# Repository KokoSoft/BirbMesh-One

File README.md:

# BirbMesh-One :bird:

The goal of **Birb**s **Mesh**tastic **One** Watt node project was to create an inexpensive and as small as possible Meshtastic node equipped with a 1 W radio module. An important aspect, from my perspective, is ensuring favorable operating conditions for the battery to extend its lifespan. The project supports multiple configuration variants, and the final functionality depends on the components you choose to solder. The core of the design is the energy‑efficient *nRF52840* controller mounted on a ProMicro board. The project is pin‑compatible with [xiaoWa_pcb](https://github.com/gargomoma/xiaoWa_pcb) and [FakeTec](https://github.com/gargomoma/fakeTec_pcb), which means no custom firmware is required.

**Key features**:
- Compact PCB: 27 × 47 mm
- Support for radio modules: E22(M), Ra‑01SH‑P, HT‑RA62
- Optional LCD and user button support
- Optional battery charging control (hardware or software)
- Optional battery voltage monitoring

## Project Description

The project was inspired by the [ikona nano](https://github.com/ndoo/ikoka-nano-meshtastic-device) and [xiaoWa_pcb](https://github.com/gargomoma/xiaoWa_pcb). The former is based on the Seeed Studio XIAO BLE, which is significantly more expensive than the ProMicro and offers fewer available GPIO pins. Additionally, the board is large and includes connectors for the battery and solar panel, which I found unnecessary. A notable strength is the correct implementation of the power supply for the boost converter that generates the supply voltage for the radio module. Another benefit, in my opinion, is the integration of the converter directly on the PCB, which allows it to be controlled programmatically. This makes it possible to switch it off to save energy. It is a project worth recommending, and using the XIAO BLE may be a good choice for those who prefer not to rely on low‑quality ProMicro boards.

Initially, this project was created as an attempt to solve the power‑supply issue present in xiaoWa_pcb, which requires a connected battery for proper operation. The boost converter powering the radio module draws energy directly from the battery connector. Without a battery, the system is powered solely by the *TP4054* charger IC, which has current limiting and built‑in protections. Although the charging current is configurable, it may be reduced to 1/10 of the set value under certain conditions, making it impossible to use the board with external power only. Using the inexpensive *HW‑085* boost converter module is an interesting idea and certainly simplifies building the device. Unfortunately, it cannot be switched off to save power.

<details>
<summary>Notes from the TP4054 datasheet</summary>

</details>

### Power Supply

There are three possible ways to power the radio module:

#### 1. Power from the ProMicro

To properly power the radio module and minimize energy loss, power must be taken from the switching circuit that selects power between USB voltage (*VBUS*) and battery voltage (*VBAT*). On the schematic, this point is labeled **VDDH**. This ensures that neither the battery nor the charger IC is loaded when device is powered from USB. You must route wire from the indicated point on the ProMicro board to the VDDH pad.

<sub>Image created using a photo from the [nrf52840‑promicro](https://github.com/sasodoma/nrf52840-promicro) repository by [sasodoma](https://github.com/sasodoma).

Optionally, if you want to supply 5 V externally (through connector `J1`) without using USB socket, connect the VBUS pad as well.

#### 2. Independent power‑switching circuit

If you prefer not to draw high current through the questionable‑quality components on the ProMicro, you can build your own voltage‑switching circuit. To do this, solder components `Q1` and `D1`. You must also connect the VBUS pad to allow powering the radio from USB.

#### 3. Compatibility mode with xiaoWa_pcb

If you want to minimize soldering and always use the device with battery connected, you can use this compatibility mode. Short the `JP1` jumper on the bottom of the PCB. The radio will be powered directly from the battery, which will load the charger IC too.

### Boost Converter

High‑power radio modules require a 5 V supply to operate at full output power. This voltage is provided by a boost converter. If you are ordering an assembled board or are comfortable with soldering, the best solution is to build the converter using the *MT3608* IC. Populate components `L1`, `U4`, `D3`, `R11`, `R12`, `C7`, and `C9`.

Alternatively, to avoid soldering small components, you may use the *HW‑085* boost module. In its default configuration, it cannot be disabled to reduce power consumption. However, the project allows adding power control: cut jumper `JP7` (shorted by default) and solder `Q3`, `Q4`, and `R13`.

> [!NOTE]
> If you plan to use a radio module that does not require 5 V (e.g., *HT‑RA62*) or do not need full transmit power, you may omit the boost converter.

### Radio Module

Based on my experience with Meshtastic networks, using an 868 MHz SAW filter significantly improves reception quality, though they have low power tolerance. Cavity filters, on the other hand, are large and expensive. In Europe, the *E22P‑868M30S* module appears to be an ideal solution, offering a built‑in receive‑path filter and high transmit power.

#### E22 / E22P Module

The module supports a wide supply range of 3.3 -- 5 V. Full transmit power requires ≥5 V, so a boost converter is necessary. If full power is not required, you may omit the converter and short *VIN* to *VOUT*. The supply voltage will then equal the battery voltage or approximately 4.7 V when externally powered.

The *T/R CTRL* (*RXEN*) pin is controlled by *SX126x* *DIO2*. The *EN* (*TXEN*) pin is controlled by nRF `P0.17`.

#### Ra‑01SH‑P Module

This module is a cheaper alternative to the E22 series, offering 29/31 dBm output power. However, **it does not include a TCXO**. To achieve full power, 5 V must be supplied to the *VCCPA* pin, requiring a boost converter and shorting pads 1–2 on `JP6`.

> [!IMPORTANT]
> The modules documentation states: _"In the default BOM configuration of the Ra‑01SH‑P module, PA is powered by the 3V3 pin of the module, and the VCCPA pin can be left floating."_

#### HT‑RA62 Module

This module is powered from the ProMicro **EXTVCC** 3.3 V rail. No boost converter is required. Short pads 2–3 on `JP6` to connect *DIO2* to *TXEN*.

### Battery Voltage Monitoring (optional)

The monitoring circuit uses two comparators with hysteresis. U1 (*MIC841H*) asserts reset when battery voltage drops below 3.6 V (\~20% charge). Reset is released above 3.7 V (\~30%).

`U2` limits the maximum charge level. When voltage exceeds 4.05 V (\~80%), the `PROG` pin of the *TP4054* charger is disconnected.

To enable charge control, remove the charging‑current‑setting resistor from the ProMicro.

<sub>Image created using a photo from the [nrf52840‑promicro](https://github.com/sasodoma/nrf52840-promicro) repository by [sasodoma](https://github.com/sasodoma).

Charging current is set by resistor `R8`.

Comparator thresholds are configured using the resistor divider `R2–R5`. Capacitor `C1` filters voltage fluctuations during radio transmission to prevent unwanted resets.

If you do not want hardware‑level reset and charge control but still want battery‑level monitoring in software, install only `R1` and `R2`.

#### Charge Control

To control charging from firmware:

- Remove the charging‑current‑setting resistor from the ProMicro.
- Install `R8` to set the desired charging current.
- Short `JP5` or install `Q2`.

## Ordering the PCBs
## Preparing firmware
## Soldering

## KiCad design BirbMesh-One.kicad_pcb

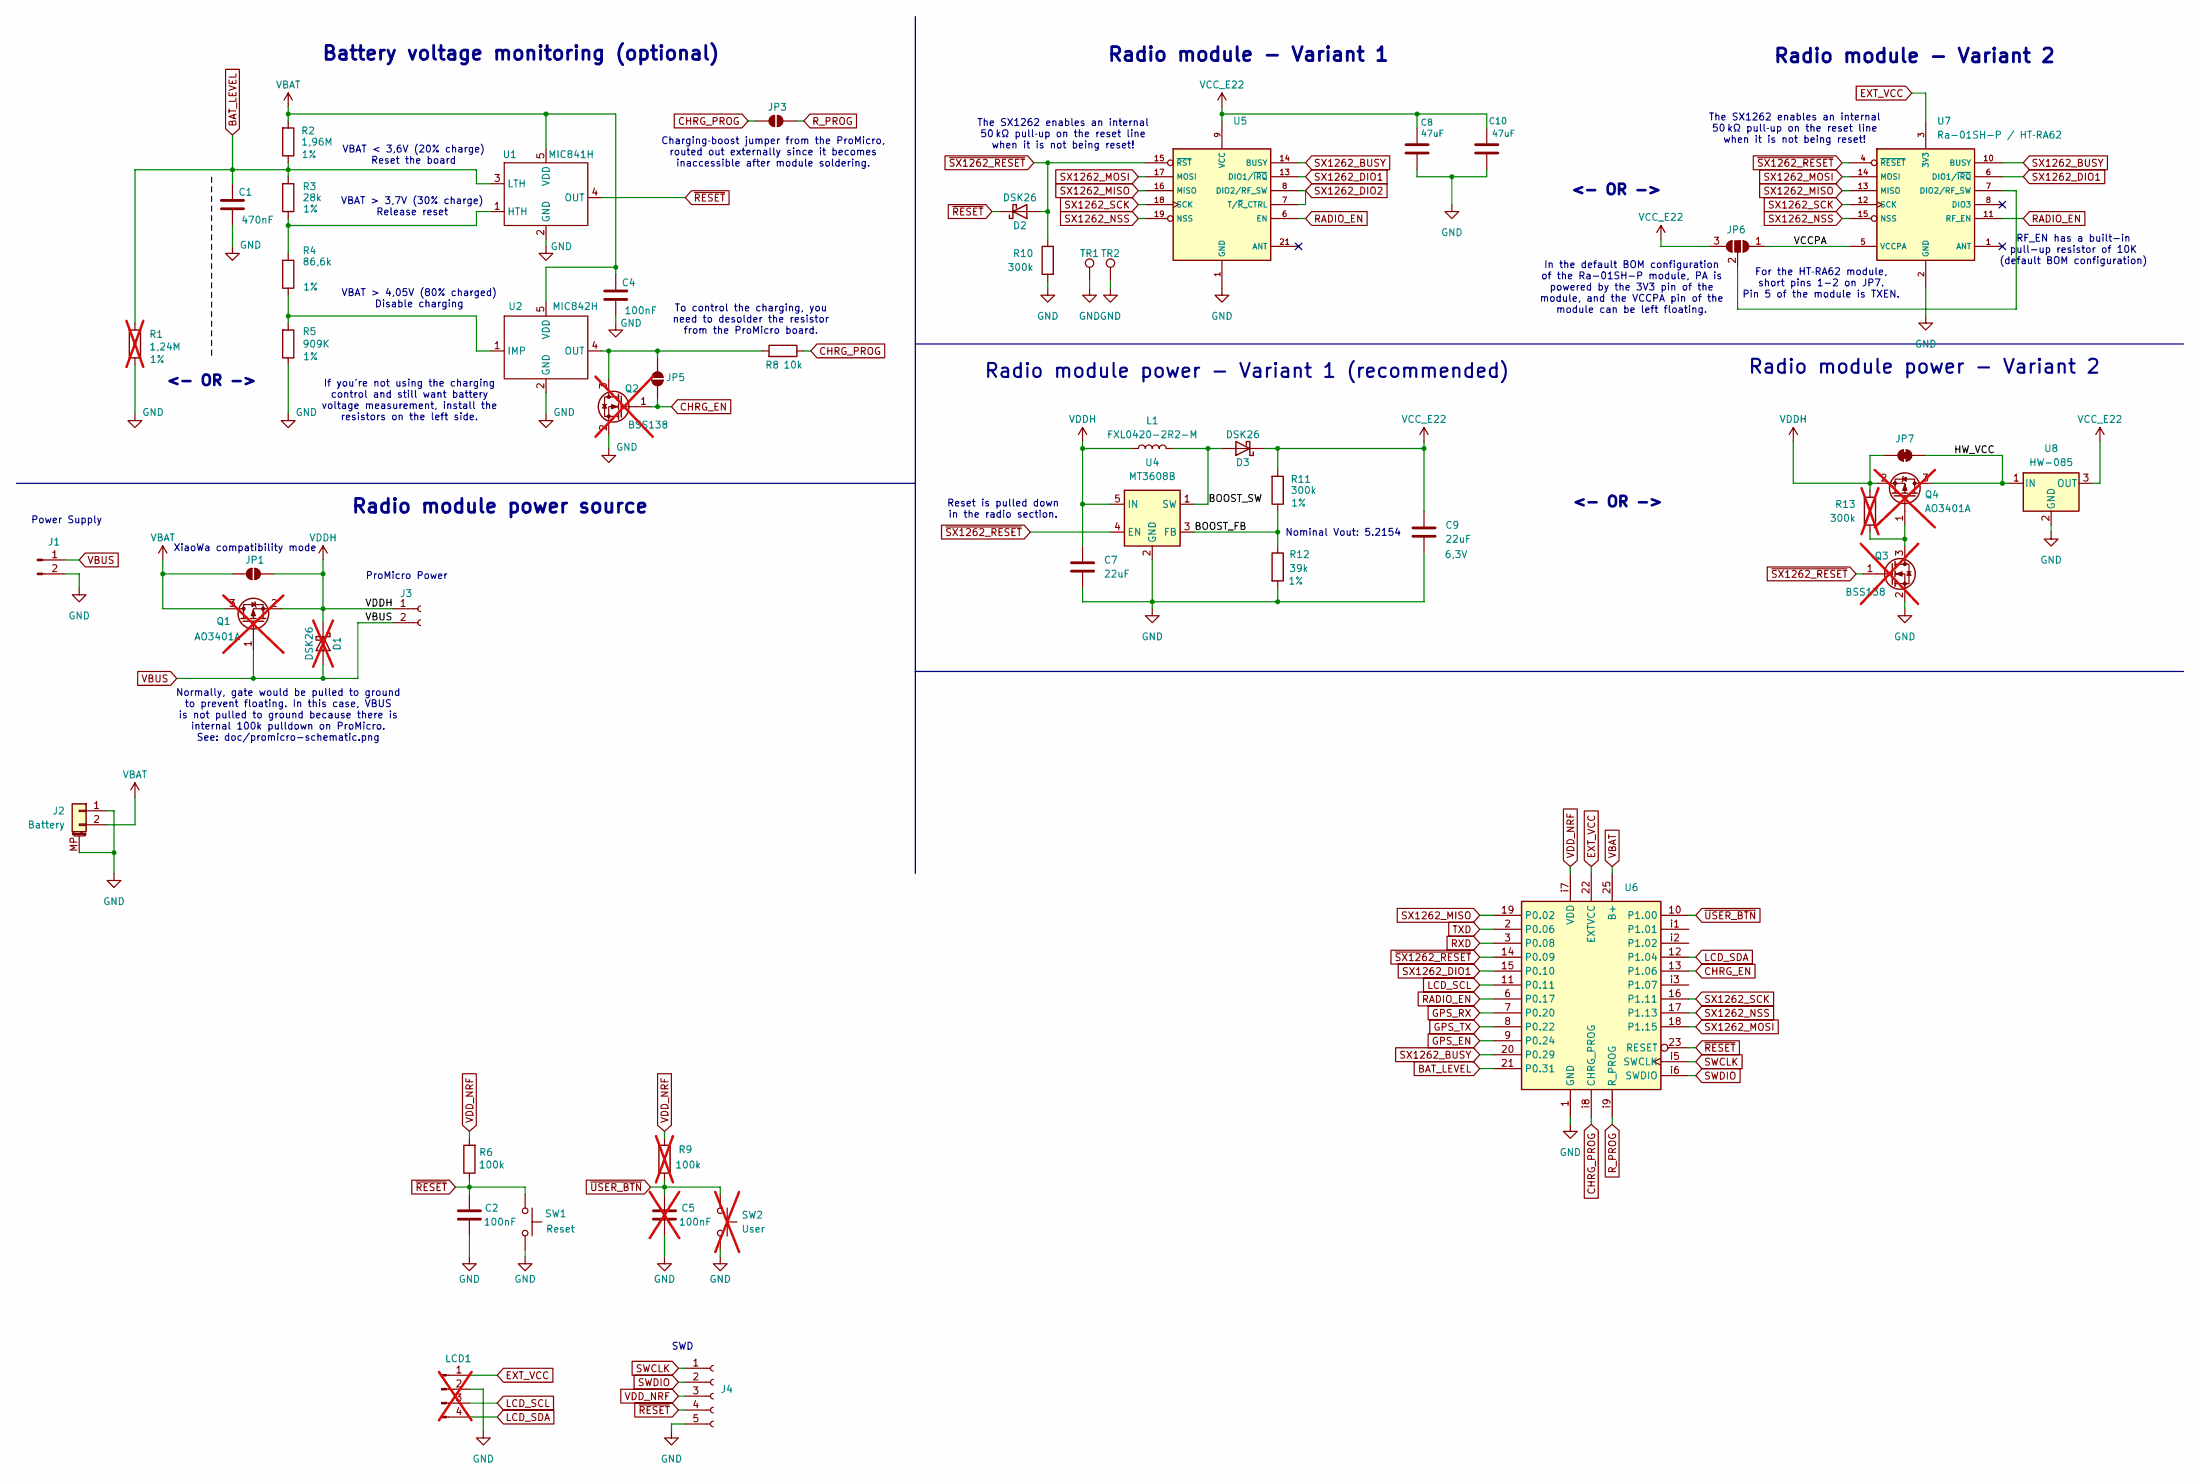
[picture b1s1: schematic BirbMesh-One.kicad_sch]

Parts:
C1: 470nF; C_0603_1608Metric_Pad1.08x0.95mm_HandSolder; Voltage 6,3V
C2: 100nF; C_0603_1608Metric_Pad1.08x0.95mm_HandSolder
C4: 100nF; C_0603_1608Metric_Pad1.08x0.95mm_HandSolder; Voltage 6,3V
C5: 100nF; C_0603_1608Metric_Pad1.08x0.95mm_HandSolder; not fitted
C7: 22uF; C_0603_1608Metric_Pad1.08x0.95mm_HandSolder; MPN CL10A226MQ8NRNC; LCSC C59461
C8, C10: 47uF; C_0805_2012Metric_Pad1.18x1.45mm_HandSolder; MPN CL31A107MQHNNNE; LCSC C15008
C9: 22uF; C_0603_1608Metric_Pad1.08x0.95mm_HandSolder; Voltage 6,3V; MPN CL10A226MQ8NRNC; LCSC C59461
D1: DSK26; D_SOD-123F; LCSC C7502712; not fitted
D2, D3: DSK26; D_SOD-123F; LCSC C7502712
J1: Conn_01x04_Pin; PinHeader_1x02_P2.54mm_Vertical
J2: Battery; JST_PH_S2B-PH-SM4-TB_1x02-1MP_P2.00mm_Horizontal
J3: Conn_01x02_Socket; PinHeader_1x02_P2.54mm_Vertical
J4: Conn_01x05_Socket; PinHeader_1x05_P1.27mm_Vertical
JP1, JP3, JP5: SolderJumper_2_Open; SolderJumper-2_P1.3mm_Open_TrianglePad1.0x1.5mm
JP6: SolderJumper_3_Open; SolderJumper-3_P1.3mm_Open_RoundedPad1.0x1.5mm
JP7: SolderJumper_2_Bridged; SolderJumper-2_P1.3mm_Bridged_Pad1.0x1.5mm
L1: FXL0420-2R2-M; L_Changjiang_FXL0420; MPN SMMS0650-220M; LCSC C167860
LCD1: Conn_01x04_Pin; PinHeader_1x04_P2.54mm_Vertical; not fitted
Q1, Q4: AO3401A; SOT-23; LCSC C15127; not fitted
Q2, Q3: BSS138; SOT-23; not fitted
R1: 1,24M; R_0603_1608Metric_Pad0.98x0.95mm_HandSolder; Tolerance 1%; not fitted
R2: 1,96M; R_0603_1608Metric_Pad0.98x0.95mm_HandSolder; Tolerance 1%
R3: 28k; R_0603_1608Metric_Pad0.98x0.95mm_HandSolder; Tolerance 1%
R4: 86,6k; R_0603_1608Metric_Pad0.98x0.95mm_HandSolder; Tolerance 1%
R5: 909K; R_0603_1608Metric_Pad0.98x0.95mm_HandSolder; Tolerance 1%
R6: 100k; R_0603_1608Metric_Pad0.98x0.95mm_HandSolder
R8: 10k; R_0603_1608Metric_Pad0.98x0.95mm_HandSolder
R9: 100k; R_0603_1608Metric_Pad0.98x0.95mm_HandSolder; not fitted
R10: 300k; R_0603_1608Metric_Pad0.98x0.95mm_HandSolder; MPN 0603WAF1502T5E
R11: 300k; R_0603_1608Metric_Pad0.98x0.95mm_HandSolder; Tolerance 1%
R12: 39k; R_0603_1608Metric_Pad0.98x0.95mm_HandSolder; Tolerance 1%; LCSC C22843
R13: 300k; R_0603_1608Metric_Pad0.98x0.95mm_HandSolder; MPN 0603WAF1502T5E; not fitted
SW1: Reset; SW_Push_SPST_NO_Alps_SKRK
SW2: User; SW_Push_SPST_NO_Alps_SKRK; LCSC C318884; not fitted
TR1, TR2: PTH; PinSocket_1x01_P2.54mm_Vertical
U1: MIC841H; SOT-353_SC-70-5
U2: MIC842H; SOT-353_SC-70-5
U4: MT3608B; SOT-23-6; LCSC C2932326
U5: E22P-868M30S
U6: ProMicro-all-pins_smd
U7: Ra-01SH-P / HT‑RA62; Ra-01SH-P
U8: HW-085

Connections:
/BOOST_FB: R11.1, R12.1, U4.3 (FB)
/BOOST_SW: D3.2 (A), L1.2, U4.1 (SW)
/HW_VCC: JP7.2 (B), Q4.3 (D), U8.1 (IN)
/VCCPA: JP6.1 (A), U7.5 (VCCPA)
BAT_LEVEL: C1.1, R1.2, R2.1, R3.2, U1.3 (LTH), U6.21 (P0.31)
CHRG_EN: JP5.1 (A), Q2.1 (G), U6.13 (P1.06)
CHRG_PROG: JP3.1 (A), R8.1, U6.i8 (CHRG_PROG)
EXT_VCC: LCD1.1, U6.22 (EXTVCC), U7.3 (3V3)
GND: C1.2, C2.1, C4.2, C5.1, C7.2, C8.1, C9.2, C10.1, J1.2, J2.1, J2.MP (MountPin), J4.5, LCD1.2, Q2.2 (S), Q3.2 (S), R1.1, R5.1, R10.2, R12.2, SW1.1, SW2.2, TR1.1, TR2.1, U1.2 (GND), U2.2 (GND), U4.2 (GND), U5.1 (GND), U6.1 (GND), U7.2 (GND), U8.2 (GND)
GPS_EN: U6.9 (P0.24)
GPS_RX: U6.7 (P0.20)
GPS_TX: U6.8 (P0.22)
LCD_SCL: LCD1.3, U6.11 (P0.11)
LCD_SDA: LCD1.4, U6.12 (P1.04)
unnamed: JP5.2 (B), Q2.3 (D), R8.2, U2.4 (OUT)
unnamed: JP6.2 (C), U7.7 (DIO2/RF_SW)
unnamed: Q3.3 (D), Q4.1 (G), R13.2
unnamed: R3.1, R4.2, U1.1 (HTH)
unnamed: R4.1, R5.2, U2.1 (IMP)
RADIO_EN: U5.6 (EN), U6.6 (P0.17), U7.11 (RF_EN)
RXD: U6.3 (P0.08)
R_PROG: JP3.2 (B), U6.i9 (R_PROG)
SWCLK: J4.1, U6.i5 (SWCLK)
SWDIO: J4.2, U6.i6 (SWDIO)
SX1262_BUSY: U5.14 (BUSY), U6.20 (P0.29), U7.10 (BUSY)
SX1262_DIO1: U5.13 (DIO1/~IRQ), U6.15 (P0.10), U7.6 (DIO1/~IRQ)
SX1262_DIO2: U5.7 (T/~R_CTRL), U5.8 (DIO2/RF_SW)
SX1262_MISO: U5.16 (MISO), U6.19 (P0.02), U7.13 (MISO)
SX1262_MOSI: U5.17 (MOSI), U6.18 (P1.15), U7.14 (MOSI)
SX1262_NSS: U5.19 (NSS), U6.17 (P1.13), U7.15 (NSS)
SX1262_SCK: U5.18 (SCK), U6.16 (P1.11), U7.12 (SCK)
TXD: U6.2 (P0.06)
VBAT: C4.1, J2.2, JP1.1 (A), Q1.3 (D), R2.2, U1.5 (VDD), U2.5 (VDD), U6.25 (B+)
VBUS: D1.2 (A), J1.1, J3.2, Q1.1 (G)
VCC_E22: C8.2, C9.1, C10.2, D3.1 (K), JP6.3 (B), R11.2, U5.9 (VCC), U8.3 (OUT)
VDDH: C7.1, D1.1 (K), J3.1, JP1.2 (B), JP7.1 (A), L1.1, Q1.2 (S), Q4.2 (S), R13.1, U4.5 (IN)
VDD_NRF: J4.3, R6.2, R9.2, U6.i7 (VDD)
~RESET: C2.2, D2.1 (K), J4.4, R6.1, SW1.2, U1.4 (OUT), U6.23 (RESET)
~SX1262_RESET: D2.2 (A), Q3.1 (G), R10.1, U4.4 (EN), U5.15 (~RST), U6.14 (P0.09), U7.4 (~RESET)
~USER_BTN: C5.2, R9.1, SW2.1, U6.10 (P1.00)

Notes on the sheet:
Radio module - Variant 2
For the HT‑RA62 module, short pins 1-2 on JP7. Pin 5 of the module is TXEN.
To control the charging, you need to desolder the resistor from the ProMicro board.
The SX1262 enables an internal 50 kΩ pull‑up on the reset line when it is not being reset!
SWD
VBAT > 4,05V (80% charged) Disable charging
Radio module power - Variant 1 (recommended)
Radio module - Variant 1
<- OR ->
VBAT > 3,7V (30% charge) Release reset
Radio module power source
Battery voltage monitoring (optional)
Radio module power - Variant 2
XiaoWa compatibility mode
Power Supply
Normally, gate would be pulled to ground to prevent floating. In this case, VBUS is not pulled to ground because there is internal 100k pulldown on ProMicro. See: doc/promicro-schematic.png
Charging‑boost jumper from the ProMicro, routed out externally since it becomes inaccessible after module soldering.
Reset is pulled down in the radio section.
ProMicro Power
In the default BOM configuration of the Ra-01SH-P module, PA is powered by the 3V3 pin of the module, and the VCCPA pin of the module can be left floating.
VBAT < 3,6V (20% charge) Reset the board
Nominal Vout: 5.2154
RF_EN has a built-in pull-up resistor of 10K (default BOM configuration)
If you're not using the charging control and still want battery voltage measurement, install the resistors on the left side.

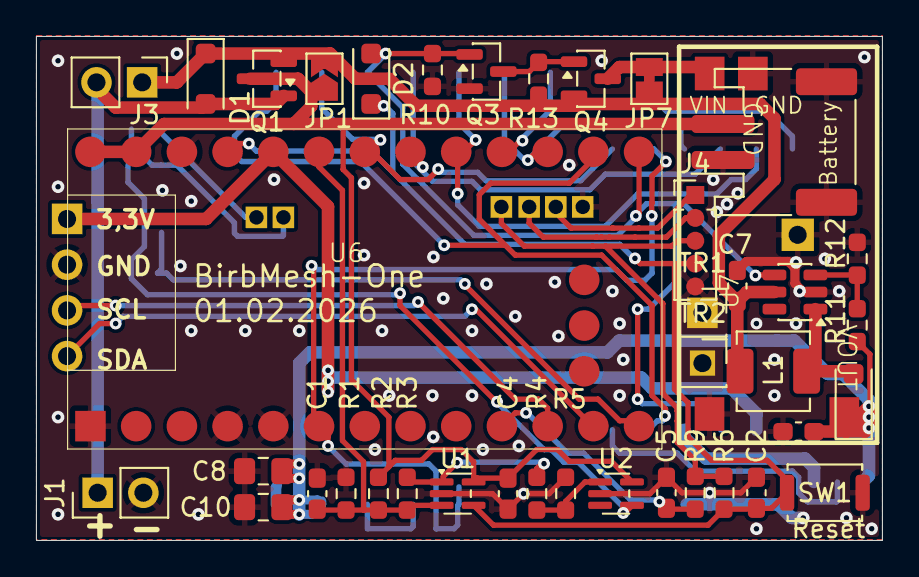
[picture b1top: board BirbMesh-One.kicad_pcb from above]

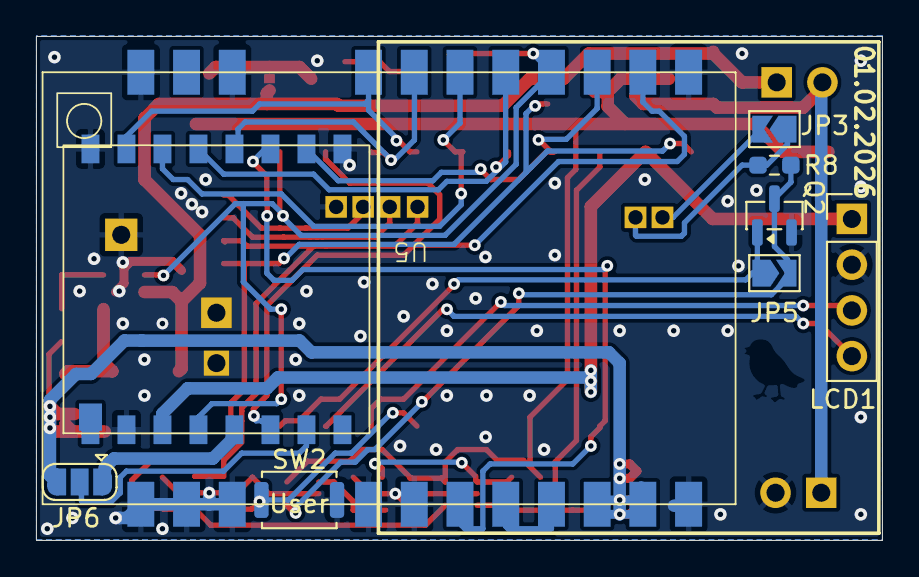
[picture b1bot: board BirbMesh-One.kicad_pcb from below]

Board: 2 copper layers, 47.0 x 28.0 mm, 49 parts (9 on the bottom side), 35 nets.

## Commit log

2026-01-21 Add LICENSE file
2026-01-21 ignore
2026-01-21 doc: Add datasheet for nRF52, E22 and ProMicro schematic
    Add full dump of available download files for E22P-868M30S module.
    Add datasheet for nRF52840.
    Add schematic for chinese ProMicro.
2026-02-01 symbols: Add symbol for MIC841 and MIC842
    The MIT841 is a comparator with 1.25% Reference and Adjustable
    Hysteresis. The device is intended for voltage monitoring applications.
    External resistors are used to set the voltage monitor threshold. When
    the threshold is crossed, the outputs switch polarity.
    The MIC842 incorporates a voltage reference and comparator with fixed
    internal hysteresis.
2026-02-01 symbols: Add symbol and footprint for E22P-868M30S
    The E22P-xxxM30S series module is a surface-mount LoRa™ wireless module
    independently developed based on the Semtech high-performance RF chip
    SX126x. It has a maximum power of 30dBm and is suitable for the
    433/868/915 MHz frequency band. It uses an industrial-grade
    high-precision active temperature-compensated crystal oscillator
    internally.
2026-02-01 symbols: footprints: Add symbols for ProMicro and HW-085
    Add symbol and footprints for ProMicro board.
    Add footprint for HW-085.
2026-02-01 symbols: Add symbol and footprint for Ra-01SH-P
    Ra-01SH-P is a LoRa series module designed and developed by Shenzhen
    Ai-Thinker Technology Co., Ltd.
2026-02-01 symbols: Add E22 thermal footprint
    The E22P-868M30S radio module has a grid of thermal pads on the
    underside, which are not included in the documentation or the official
    footprint. Add a new E22P-868M30S-thermal footprint that includes the
    thermal pads.
2026-02-01 sch: pcb: BirbMesh-One Alpha
    First version of the schematic and printed circuit board project.
2026-02-01 doc: Add datasheet for MIC841 and MIC842
    Add datasheet for MIT841/MIT842 comparator with 1.25% Reference and
    Adjustable Hysteresis.
    Add a spreadsheet that allows calculating the resistor values for the
    resistive voltage divider used in the project for the battery voltage
    monitor.
2026-02-01 doc: Add datasheets for components used on the Pro Micro board
    Add datasheets for the TP4054 Li‑Po charger and the ME6217 LDO used on
    the ProMicro board.
2026-02-01 doc: Add datasheet for MT3608
    The MT3608 is a constant frequency, 6-pin SOT23 current mode step-up
    converter intended for small, low power applications. The MT3608
    switches at 1.2MHz and allows the use of tiny, low cost capacitors and
    inductors 2mm or less in height. Internal soft-start results in small
    inrush current and extends battery life.
2026-02-01 doc: Add datasheet for Ra-01SH-P
    Ra-01SH-P is a LoRa series module designed and developed by Shenzhen
    Ai-Thinker Technology Co., Ltd.
2026-02-04 readme: Add project description
